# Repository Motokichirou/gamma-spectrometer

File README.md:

<h1 align="center">Гамма-спектрометр на NaI(Tl)</h1>

<p align="center">

</p>

<!-- README-I18N:START -->
<p align="center"><b>Русский</b> | <a href="./README.en.md">English</a></p>
<!-- README-I18N:END -->

Портативный цилиндрический гамма-спектрометр на кристалле NaI(Tl) Ø63×63 мм и ФЭУ Hamamatsu R1307, с интерфейсом USB-C, совместимым с [BecqMoni](https://github.com/Am6er/BecqMoni) / AtomSpectra (протокол shproto).

> 📚 **Документация:** [обзор аппаратной части](docs/ru/hardware.md) · [прошивка](docs/ru/firmware.md) · [протокол shproto](docs/ru/protocol.md) · [ПО на PC](host/README.md)

> ✅ **Ноябрь 2026: прибор собран и работает с BecqMoni** на штатном детекторе NaI(Tl) Ø63×63 + R1307 (ФЭУ ~565 В):
> **Cs-137 6.7–6.9 % FWHM**. Разбор хвостовых наложений в прошивке: на смеси ~20 кимп/с принимается ~17 400 имп/с
> без потери разрешения; поправка нелинейности кодов АЦП (DNL). Подробности — журнал [`SPEC.md`](firmware/board_g474cb/SPEC.md) §10.

---

## Ключевые характеристики

| Параметр | Значение |
|---|---|
| Детектор | NaI(Tl) Ø63×63 мм |
| ФЭУ | Hamamatsu R1307 (8 каскадов, Ø76 мм) |
| Диапазон энергий | ≈20 кэВ (порог 18 кодов) – ≈3.8 МэВ (насыщение АЦП) |
| FWHM @ Cs-137 | **6.7–6.9 % измерено** (штатный NaI 63×63 + R1307, ВВ ~565 В) |
| Каналов спектра | 8192 |
| Скорость счёта | до ~30 000 имп/с |
| МК | STM32G474CBT6 (LQFP-48) @ 156 МГц, 12-бит АЦП (сигнал 3.47 Мвыб/с), встроенные ОУ |
| ВВ питание | 0 … −1200 В, рабочее ~565 В на штатном ФЭУ (MAX1847 + 4-ступенчатый умножитель CW) |
| Интерфейс | USB-C → UART 600 кбит/с (FT231X), протокол shproto |
| Питание | USB 5 В, ~370 мА |
| Форм-фактор | Цилиндрический стек, платы Ø45 мм |

---

## Аппаратная архитектура

### Стек плат (снизу → вверх)

```
 ┌─────────────────────────────────────────┐
 │  USB/Power board  Ø45 mm               │  ← кабель USB-C
 │  LP5907 · AMS1117 · TPS60400 · FT231X  │
 ├─────────────────────────────────────────┤
 │  HV board         Ø45 mm               │
 │  MAX1847 · IRLML0060 · CW ×4 · ≤−1200 V│
 ├─────────────────────────────────────────┤
 │  MCU board        Ø45 mm               │
 │  STM32G474CBT6 · шейпер · ADC · SPI    │
 ├─────────────────────────────────────────┤
 │  Divider board    Ø42–45 mm            │  ← ФЭУ Hamamatsu R1307 + NaI(Tl)
 │  R1307 divider · MMBTA42 buffers       │
 │  ADA4817-1 TIA (Zt = 2.7 kΩ)           │
 └─────────────────────────────────────────┘
```

Межплатные соединения — без разъёмов:
- **Шина стека**: цанговые пины Ø1.5 мм на дуге R20 мм, соосные на всех платах (44 посадочных
  места: USB 11, ВВ 15, МК 13, делитель 5); по ней же идёт питание делителя ±5 В_A
- **Сигнал** (делитель → МК): тонкий коаксиал, припаянный к пятакам
- **−HV**: экранированный провод ≥5 кВ (ВВ → делитель) через отверстие Ø4.5 мм в плате МК
- **Pt1000** на корпусе кристалла: витая пара на пятаки платы МК
- Механика: по три стойки M2.5 в центре каждой платы

### Цепь сигнала

```
NaI(Tl) + R1307            Плата делителя                 Плата МК
─────────────    ─────────────────────────────   ──────────────────────────────────
 Сцинтилляция →   Делитель (цепочка 7.72 МОм)   →  OPAMP1: интегратор, τ=1 мкс
 τ_спада=230 нс   Активные буферы (Dy6/7/8)        OPAMP2: интегратор, τ=1.8 мкс
 ФЭУ на ~565 В    ADA4817 TIA, Zt=2.7 кОм       →  PGA ×4 (OPAMP3)
                                                   V_ADC = baseline 0.394 В
                                                   ADC3_IN1, 3.47 Мвыб/с
                                                   импульс: фронт 5–6 отсчётов, FWHM 3.6 мкс
                                                   амплитуда по эталону формы (64 фазы)
                                                   гистограмма 8192 кан. → USB
```

**Полярность АЦП:** анод забирает ток ⇒ выход TIA вверх ⇒ импульсы **положительны** относительно baseline 0.394 В → `amplitude = sample − baseline`

### Калибровка энергии (измерено на прежнем временном детекторе NaI 40×40, ~755 В, Ra-226)

Калибровка по 5 точкам в BecqMoni: `E[кэВ] = −6.01 + 0.5518·x + 6.63·10⁻⁶·x²` (x — канал).
Изгиб шкалы — в основном непропорциональность световыхода NaI, а не электроника.

| Линия | Энергия | Канал / 8192 | Найдено по калибровке |
|---|---|---|---|
| Pb-214 | 295 кэВ | 549 | 299 кэВ |
| Pb-214 | 352 кэВ | 652 | 356 кэВ |
| Bi-214 | 609 кэВ | 1102 | 610 кэВ |
| Cs-137 | 662 кэВ | ≈1194 | — |
| Bi-214 | 1120 кэВ | 1990 | 1118 кэВ |
| Bi-214 | 1764 кэВ | 3107 | 1773 кэВ |
| Потолок (насыщение АЦП) | ≈3.8 МэВ | ≈6900 | — |

Положение пиков задаётся ВВ: Cs выставляется на канал ~1160–1200 подстройкой ВВ (на штатном детекторе — ~565 В).

---

## Статус проекта

| Задача | Статус |
|---|---|
| Схемы всех 4 плат | ✅ Готово (ERC 0) |
| LTspice: TIA + активный делитель, шейпер, шум, петля ВВ | ✅ До разводки; итог подтверждён замерами на плате |
| BOM с MPN + footprint | ✅ 176 компонентов. Себестоимость прибора **6 749 ₽** деньгами (8 540 ₽ с учётом домашних запасов, без детектора) — [`docs/cost.md`](docs/cost.md) |
| Разводка PCB | ✅ 2 слоя, 4 платы в одной заготовке 187.5 × 45 мм, нормы ВВ-зазоров 3 мм/кВ в `.kicad_dru`. Плата МК переразведена под LQFP-48 (октябрь 2026) |
| Изготовление плат | ✅ Получены (ПС-Электро, 1.5 мм, без шелкографии) |
| Комплектующие | ✅ Всё получено и сверено |
| Сборка и первое включение | ✅ Стек собран, прошивка по UART через системный загрузчик, ВВ под нагрузкой, тракт исправен |
| Прошивка STM32 | ✅ Чистая прошивка [`firmware/gamma_fw/`](firmware/gamma_fw/) на плате: детектор с эталоном формы (снят с реального тракта), разбор хвостовых наложений, поправка DNL АЦП, ВВ с подстройкой, Pt1000, регистратор спектров во флешку W25Q64, настройки (v4) и калибровка во флеш, обновление по COM-порту; принимается BecqMoni. ТЗ и журнал находок — [`firmware/board_g474cb/SPEC.md`](firmware/board_g474cb/SPEC.md) |
| Доводка тракта | ✅ Шейпер переделан под длинное формирование, R417 2.7 кОм: Cs 7.8 → 6.9 % (на 40×40), ВВ 1030 → ~750 В |
| Штатный детектор NaI 63×63 + R1307 | ✅ Установлен с 2026-11-09, ВВ ~565 В, Cs-137 6.7–6.9 % FWHM. Остаётся термокомпенсация и доводка ревизии плат — [`docs/revision_todo.md`](docs/revision_todo.md) |
| ПО на PC `gammapult` | ✅ Релиз v0.7.0: сервисный пульт под боевую прошивку (GUI + CLI, единый .exe; новый интерфейс — главный экран, мастер настройки, расширенный режим): телеметрия, ВВ и подстройка по пику, калибровки монитора ВВ и Pt1000, порог/PGA, самотест линейности по ЦАП, мастера эталона формы и термокомпенсации, **прошивка голого прибора и мастер ввода в строй**, сохранение во флеш. Спектры и энергокалибровка — в BecqMoni |

---

## Структура репозитория

```
gamma-spectrometer/
├── docs/
│   ├── adc_mcu_board.md              # Плата МК v1.6 — полная техническая документация
│   ├── divider_board.md              # Плата делителя + ADA4817 TIA
│   ├── usb_power_board.md            # Плата USB/питания — обзор
│   ├── usb_power_board_schematic.md  # Плата USB/питания — детальная схема
│   ├── hv_board_schematic.md         # Плата ВВ — детальная схема
│   ├── mcu_board_bringup.md          # Запуск платы МК (первое включение, доработки)
│   ├── hv_board_bringup.md           # Запуск платы ВВ, помеха 257 кГц и экран
│   ├── assembly_notes.md             # Заметки по сборке
│   ├── fab_pselectro.md              # Требования завода и сверка
│   ├── cost.md                       # Себестоимость
│   └── ru/, en/                      # Курированная документация (RU/EN)
├── firmware/
│   ├── board_g474cb/SPEC.md          # ТЗ прошивки и журнал находок
│   └── gamma_fw/                     # Боевая прошивка (сборка build.sh, тесты на ПК, tools/gfw.py)
├── host/                             # ПО на PC `gammapult` (Win32/ImGui, GUI + CLI)
├── pcb/
│   └── gamma_spectrometer/           # Проект KiCad (все 4 платы, заготовка, герберы)
```

---

## Разрешение (измерено, Cs-137)

Строки до «Тот же детектор Sypher» включительно — на временном кристалле NaI 40×40.

| Конфигурация | FWHM |
|---|---|
| Первый тракт (импульс короче отсчёта АЦП), ~1040 В | 7.6–7.8 % |
| Шейпер V2 (фронт 5–6 отсчётов), 1030 В | 6.99 % |
| Шейпер V2 + R417 2.7 кОм, ~755 В | 7.1 % |
| То же, кристалл 40×40 с большим световыходом, 735 В | **6.9 %** |
| Тот же детектор Sypher на своей электронике (по энергии, кэВ) | 7.08 % |
| **Штатный NaI 63×63 + R1307**, ~565 В (с 2026-11-09) | **6.7–6.9 %** |

На штатном детекторе шум базы σ ≈ 2.2 кода АЦП при амплитуде Cs ≈ 595 кодов: вклад электроники
не больше ≈0.9 % FWHM (оценка сверху, подгонка по эталону ещё усредняет), а из 6.7–6.9 % на кристалл
и ФЭУ приходится ≈6.7 %. Разрешение ограничено детектором, а не трактом (на 40×40 скан ВВ давал то же:
a ≈ 7.0 %, шум ≈0.8 %). Разрешение сравнивается только по энергии: у трактов с нелинейной шкалой процент
по каналу выглядит лучше реального. Подробности — [`firmware/board_g474cb/SPEC.md`](firmware/board_g474cb/SPEC.md) §10.

---

## Протокол: shproto / AtomSpectra

Совместим с [BecqMoni](https://github.com/Am6er/BecqMoni) и [nanopro](https://github.com/Am6er/nanopro).

- UART 600 000 бит/с, 8N1
- Кадр: `0xFE | CMD | PAYLOAD (с байт-стаффингом) | CRC16-MODBUS | 0xA5`
- Cmd `0x01`: спектр (до 8192 × 32-битных каналов)
- Cmd `0x04`: статус (прошедшее время, CPS, число невалидных импульсов)
- Keep-alive: `0xFF` от ПК каждую ~1 с
- Необязательная команда `-baud` (до 3 Мбод) действует только в ОЗУ: через 5 с без кадров от хоста прибор возвращается на 600 000

Полный справочник: [docs/ru/protocol.md](docs/ru/protocol.md).

---

## Лицензия

Файлы аппаратного дизайна (KiCad, LTspice) — [CERN OHL-S v2](https://ohwr.org/cern_ohl_s_v2.txt)  
ПО (прошивка, host) — [MIT](https://opensource.org/licenses/MIT)

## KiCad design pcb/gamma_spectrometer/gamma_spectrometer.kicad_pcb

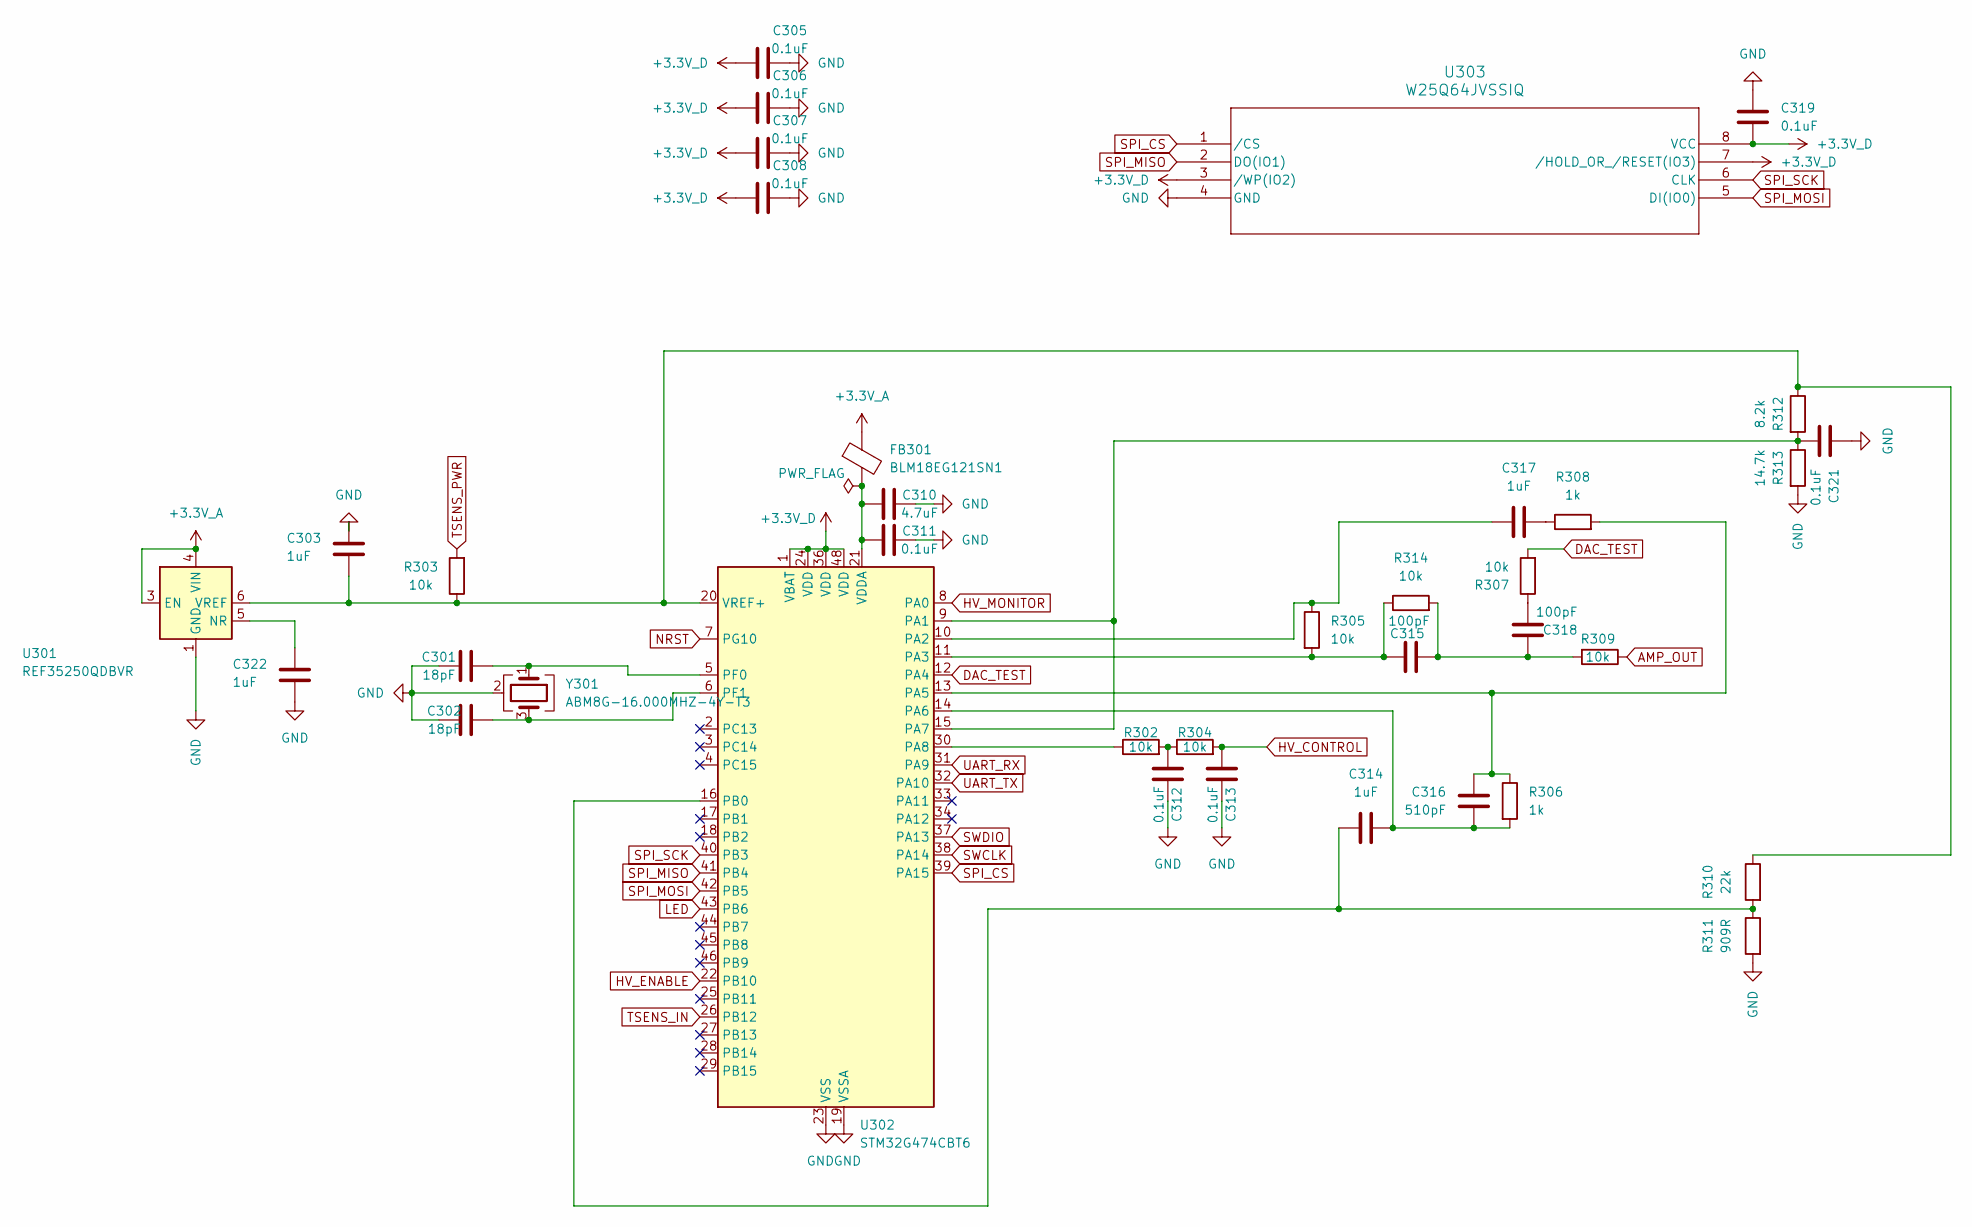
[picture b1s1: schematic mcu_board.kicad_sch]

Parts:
C301, C302: 18pF; C_0402_1005Metric_Pad0.74x0.62mm_HandSolder
C303, C322: 1uF; C_0805_2012Metric_Pad1.18x1.45mm_HandSolder
C305, C306, C307, C308, C311, C312, C313, C319, C321: 0.1uF; C_0603_1608Metric_Pad1.08x0.95mm_HandSolder
C310: 4.7uF; C_0805_2012Metric_Pad1.18x1.45mm_HandSolder
C314, C317: 1uF; C_0603_1608Metric_Pad1.08x0.95mm_HandSolder
C315, C318: 100pF; C_0603_1608Metric_Pad1.08x0.95mm_HandSolder
C316: 510pF; C_0603_1608Metric_Pad1.08x0.95mm_HandSolder
FB301: BLM18EG121SN1; L_0603_1608Metric_Pad1.05x0.95mm_HandSolder
R302, R303, R304, R305, R307, R309, R314: 10k; R_0603_1608Metric_Pad0.98x0.95mm_HandSolder
R306, R308: 1k; R_0603_1608Metric_Pad0.98x0.95mm_HandSolder
R310: 22k; R_0603_1608Metric_Pad0.98x0.95mm_HandSolder
R311: 909R; R_0603_1608Metric_Pad0.98x0.95mm_HandSolder
R312: 8.2k; R_0603_1608Metric_Pad0.98x0.95mm_HandSolder
R313: 14.7k; R_0603_1608Metric_Pad0.98x0.95mm_HandSolder
U301: REF35250QDBVR; SOT-23-6
U302: STM32G474CBT6; LQFP-48_7x7mm_P0.5mm
U303: W25Q64JVSSIQ; SOIC-8_5P28X5P28_WIN-M
Y301: ABM8G-16.000MHZ-4Y-T3; Crystal_SMD_3225-4Pin_3.2x2.5mm

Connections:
+3.3V_A: FB301.1, U301.3 (EN), U301.4 (VIN); also elsewhere on the board
+3.3V_D: C305.1, C306.1, C307.1, C308.1, C319.2, U302.1 (VBAT), U302.24 (VDD), U302.36 (VDD), U302.48 (VDD), U303.3 (/WP(IO2)), U303.7 (/HOLD_OR_/RESET(IO3)), U303.8 (VCC); also elsewhere on the board
AMP_OUT: R309.1; also elsewhere on the board
DAC_TEST: R307.2, U302.12 (PA4)
GND: C301.2, C302.2, C303.1, C305.2, C306.2, C307.2, C308.2, C310.2, C311.2, C312.2, C313.2, C319.1, C321.1, C322.2, R311.2, R313.2, U301.1 (GND), U301.2 (GND), U302.19 (VSSA), U302.23 (VSS), U302.35 (VSS), U302.47 (VSS), U303.4 (GND), Y301.2 (G), Y301.4 (G); also elsewhere on the board
HV_CONTROL: C313.1, R304.2; also elsewhere on the board
HV_ENABLE: U302.22 (PB10); also elsewhere on the board
HV_MONITOR: U302.8 (PA0); also elsewhere on the board
LED: U302.43 (PB6); also elsewhere on the board
NRST: U302.7 (PG10)
unnamed: C312.1, R302.2, R304.1
unnamed: C315.1, C318.1, R309.2, R314.2
unnamed: C317.2, R308.1
unnamed: C318.2, R307.1
unnamed: C322.1, U301.5 (NR)
unnamed: C303.2, R303.1, R310.1, R312.1, U301.6 (VREF), U302.20 (VREF+)
unnamed: C321.2, R312.2, R313.1, U302.9 (PA1), U302.15 (PA7)
unnamed: C317.1, R305.1, U302.10 (PA2)
unnamed: C315.2, R305.2, R314.1, U302.11 (PA3)
unnamed: C316.1, R306.1, R308.2, U302.13 (PA5)
unnamed: C314.2, C316.2, R306.2, U302.14 (PA6)
unnamed: R302.1, U302.30 (PA8)
unnamed: C314.1, R310.2, R311.1, U302.16 (PB0)
unnamed: C301.1, U302.5 (PF0), Y301.1
unnamed: C302.1, U302.6 (PF1), Y301.3
unnamed: C310.1, C311.1, FB301.2, U302.21 (VDDA)
SPI_CS: U302.39 (PA15), U303.1 (/CS)
SPI_MISO: U302.41 (PB4), U303.2 (DO(IO1))
SPI_MOSI: U302.42 (PB5), U303.5 (DI(IO0))
SPI_SCK: U302.40 (PB3), U303.6 (CLK)
SWCLK: U302.38 (PA14)
SWDIO: U302.37 (PA13)
TSENS_IN: U302.26 (PB12); also elsewhere on the board
TSENS_PWR: R303.2; also elsewhere on the board
UART_RX: U302.31 (PA9); also elsewhere on the board
UART_TX: U302.32 (PA10); also elsewhere on the board

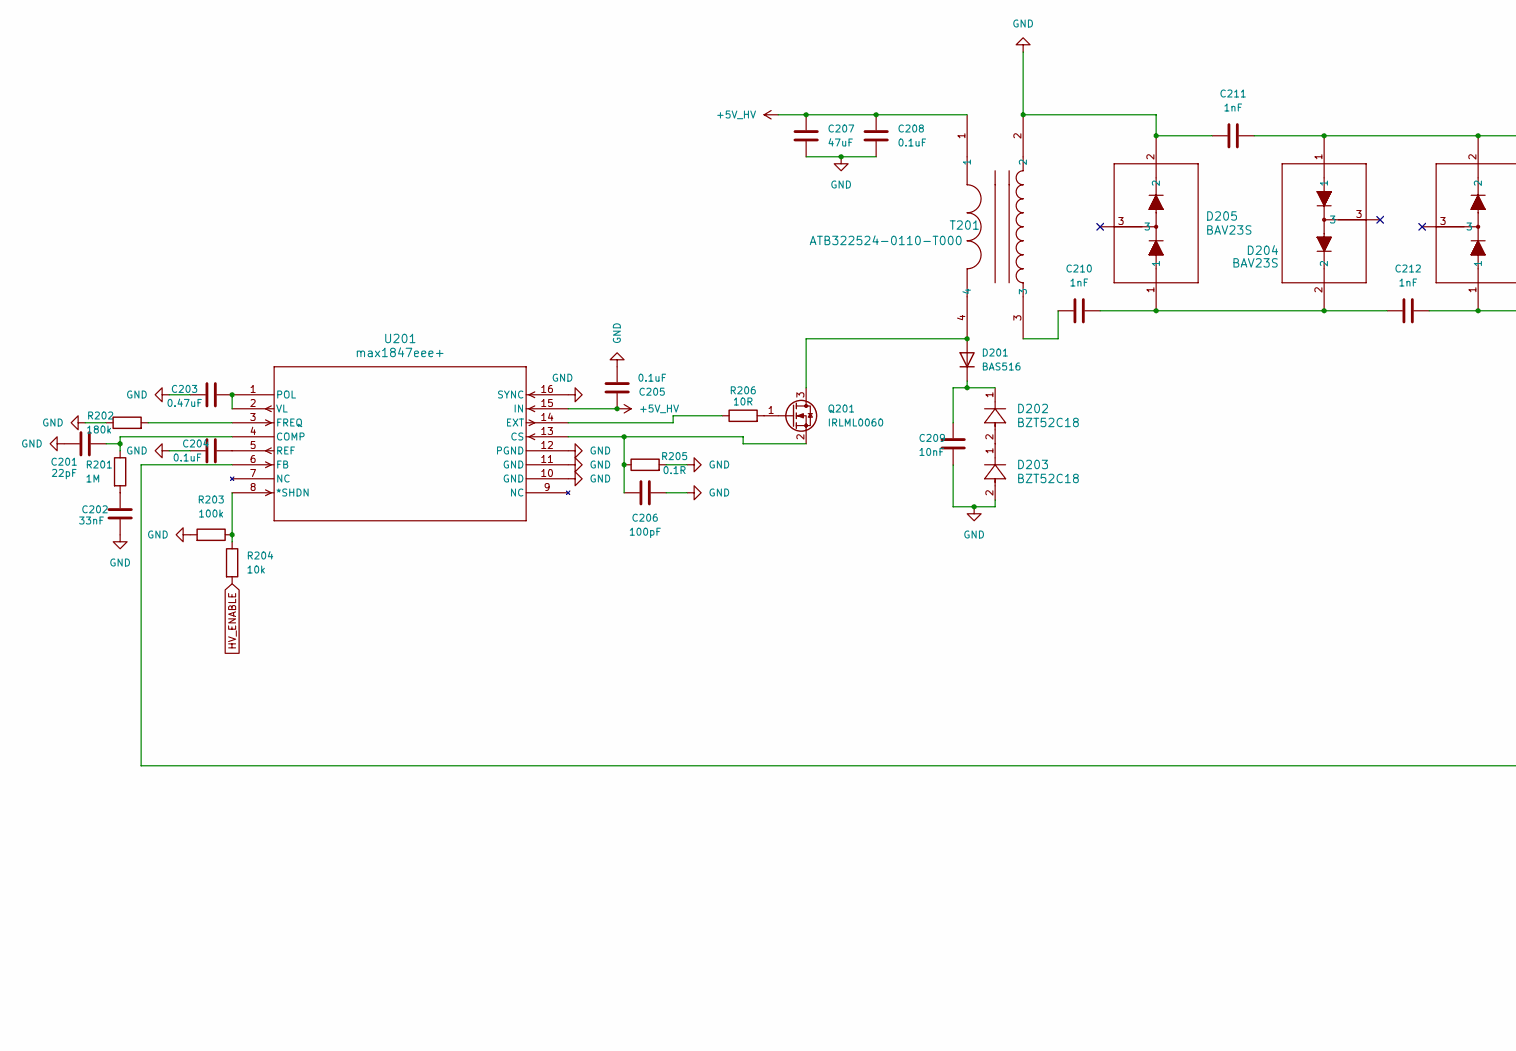
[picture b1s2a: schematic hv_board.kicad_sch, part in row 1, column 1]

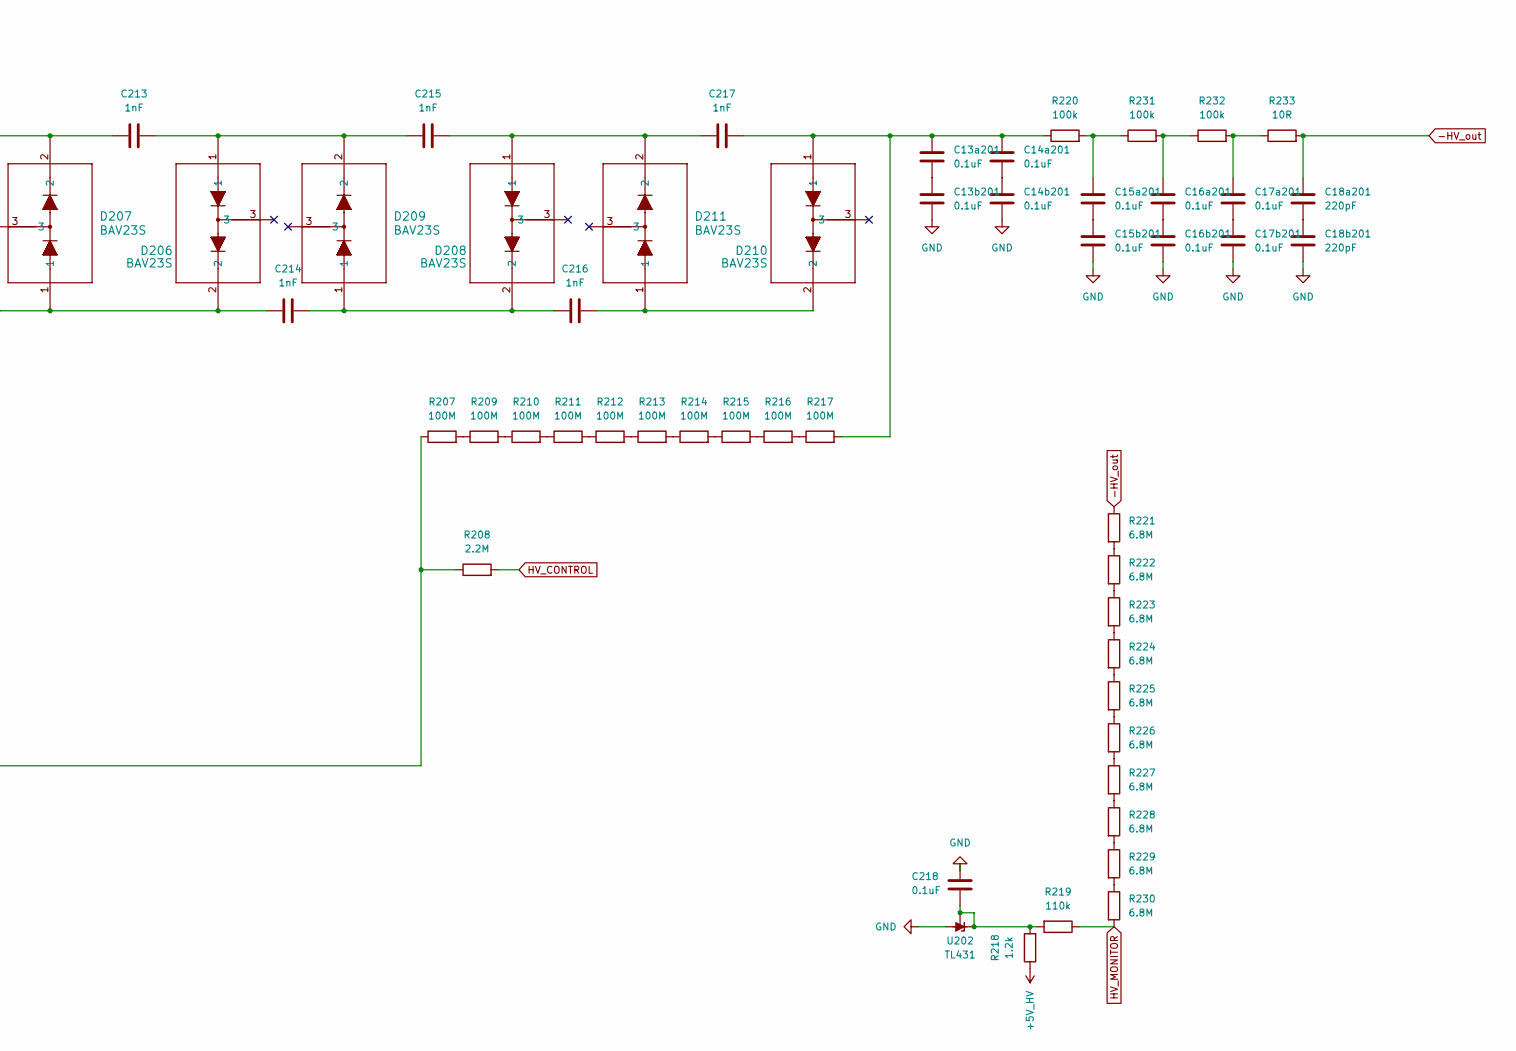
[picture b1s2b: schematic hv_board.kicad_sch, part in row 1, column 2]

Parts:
C13a201, C13b201, C14a201, C14b201, C15a201, C15b201, C16a201, C16b201, C17a201, C17b201: 0.1uF; C_1812_4532Metric_Pad1.57x3.40mm_HandSolder
C18a201, C18b201: 220pF; C_1206_3216Metric_Pad1.33x1.80mm_HandSolder
C201: 22pF; C_0402_1005Metric_Pad0.74x0.62mm_HandSolder
C202: 33nF; C_0805_2012Metric_Pad1.18x1.45mm_HandSolder
C203: 0.47uF; C_0805_2012Metric_Pad1.18x1.45mm_HandSolder
C204, C205, C208, C218: 0.1uF; C_0603_1608Metric_Pad1.08x0.95mm_HandSolder
C206: 100pF; C_0603_1608Metric_Pad1.08x0.95mm_HandSolder
C207: 47uF; C_1210_3225Metric_Pad1.33x2.70mm_HandSolder
C209: 10nF; C_0603_1608Metric_Pad1.08x0.95mm_HandSolder
C210, C211, C212, C213, C214, C215, C216, C217: 1nF; C_0805_2012Metric_Pad1.18x1.45mm_HandSolder
D201: BAS516; D_SOD-523
D202, D203: BZT52C18; D_SOD-123
D204, D205, D206, D207, D208, D209, D210, D211: BAV23S; SOT-23
Q201: IRLML0060; SOT-23
R201: 1M; R_0603_1608Metric_Pad0.98x0.95mm_HandSolder
R202: 180k; R_0603_1608Metric_Pad0.98x0.95mm_HandSolder
R203, R220, R231, R232: 100k; R_0603_1608Metric_Pad0.98x0.95mm_HandSolder
R204: 10k; R_0603_1608Metric_Pad0.98x0.95mm_HandSolder
R205: 0.1R; R_0603_1608Metric_Pad0.98x0.95mm_HandSolder
R206, R233: 10R; R_0603_1608Metric_Pad0.98x0.95mm_HandSolder
R207, R209, R210, R211, R212, R213, R214, R215, R216, R217: 100M; R_1206_3216Metric_Pad1.30x1.75mm_HandSolder
R208: 2.2M; R_0603_1608Metric_Pad0.98x0.95mm_HandSolder
R218: 1.2k; R_0603_1608Metric_Pad0.98x0.95mm_HandSolder
R219: 110k; R_0603_1608Metric_Pad0.98x0.95mm_HandSolder
R221, R222, R223, R224, R225, R226, R227, R228, R229, R230: 6.8M; R_1206_3216Metric_Pad1.30x1.75mm_HandSolder
T201: ATB322524-0110-T000; CHOKE_524-0110-T000_TDK-M
U201: max1847eee+; 21-0055H_16_MXM-M
U202: TL431; SOT-23

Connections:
+5V_HV: C205.2, C207.1, C208.1, R218.1, T201.1, U201.15 (IN); also elsewhere on the board
GND: C13b201.2, C14b201.2, C15b201.2, C16b201.2, C17b201.2, C18b201.2, C201.1, C202.2, C203.1, C204.1, C205.1, C206.2, C207.2, C208.2, C209.2, C211.1, C218.1, D203.2, D205.2, R202.1, R203.2, R205.2, T201.2, U201.10 (GND), U201.11 (GND), U201.12 (PGND), U201.16 (SYNC), U202.3 (A); also elsewhere on the board
HV_CONTROL: R208.2; also elsewhere on the board
HV_ENABLE: R204.2; also elsewhere on the board
HV_MONITOR: R219.1, R230.2; also elsewhere on the board
unnamed: C13a201.1, C14a201.1, C217.2, D210.1, R217.2, R220.1
unnamed: C13a201.2, C13b201.1
unnamed: C14a201.2, C14b201.1
unnamed: C15a201.1, R220.2, R231.1
unnamed: C15a201.2, C15b201.1
unnamed: C16a201.1, R231.2, R232.1
unnamed: C16a201.2, C16b201.1
unnamed: C17a201.1, R232.2, R233.1
unnamed: C17a201.2, C17b201.1
unnamed: C18a201.2, C18b201.1
unnamed: C202.1, R201.2
unnamed: C210.1, T201.3
unnamed: C210.2, C212.1, D204.2, D205.1
unnamed: C211.2, C213.1, D204.1, D207.2
unnamed: C212.2, C214.1, D206.2, D207.1
unnamed: C213.2, C215.1, D206.1, D209.2
unnamed: C214.2, C216.1, D208.2, D209.1
unnamed: C215.2, C217.1, D208.1, D211.2
unnamed: C216.2, D210.2, D211.1
unnamed: D201.2 (A), Q201.3 (D), T201.4
unnamed: C209.1, D201.1 (K), D202.1
unnamed: D202.2, D203.1
unnamed: Q201.1 (G), R206.2
unnamed: C206.1, Q201.2 (S), R205.1, U201.13 (CS)
unnamed: R207.2, R209.1
unnamed: R209.2, R210.1
unnamed: R210.2, R211.1
unnamed: R211.2, R212.1
unnamed: R212.2, R213.1
unnamed: R213.2, R214.1
unnamed: R214.2, R215.1
unnamed: R215.2, R216.1
unnamed: R216.2, R217.1
unnamed: R221.2, R222.1
unnamed: R222.2, R223.1
unnamed: R223.2, R224.1
unnamed: R224.2, R225.1
unnamed: R225.2, R226.1
unnamed: R226.2, R227.1
unnamed: R227.2, R228.1
unnamed: R228.2, R229.1
unnamed: R229.2, R230.1
unnamed: R203.1, R204.1, U201.8 (*SHDN)
unnamed: C201.2, R201.1, U201.4 (COMP)
unnamed: R206.1, U201.14 (EXT)
unnamed: R207.1, R208.1, U201.6 (FB)
unnamed: R202.2, U201.3 (FREQ)
unnamed: C203.2, U201.1 (POL), U201.2 (VL)
unnamed: C204.2, U201.5 (REF)
unnamed: C218.2, R218.2, R219.2, U202.1 (K), U202.2 (REF)
−HV_out: C18a201.1, R221.1, R233.2; also elsewhere on the board

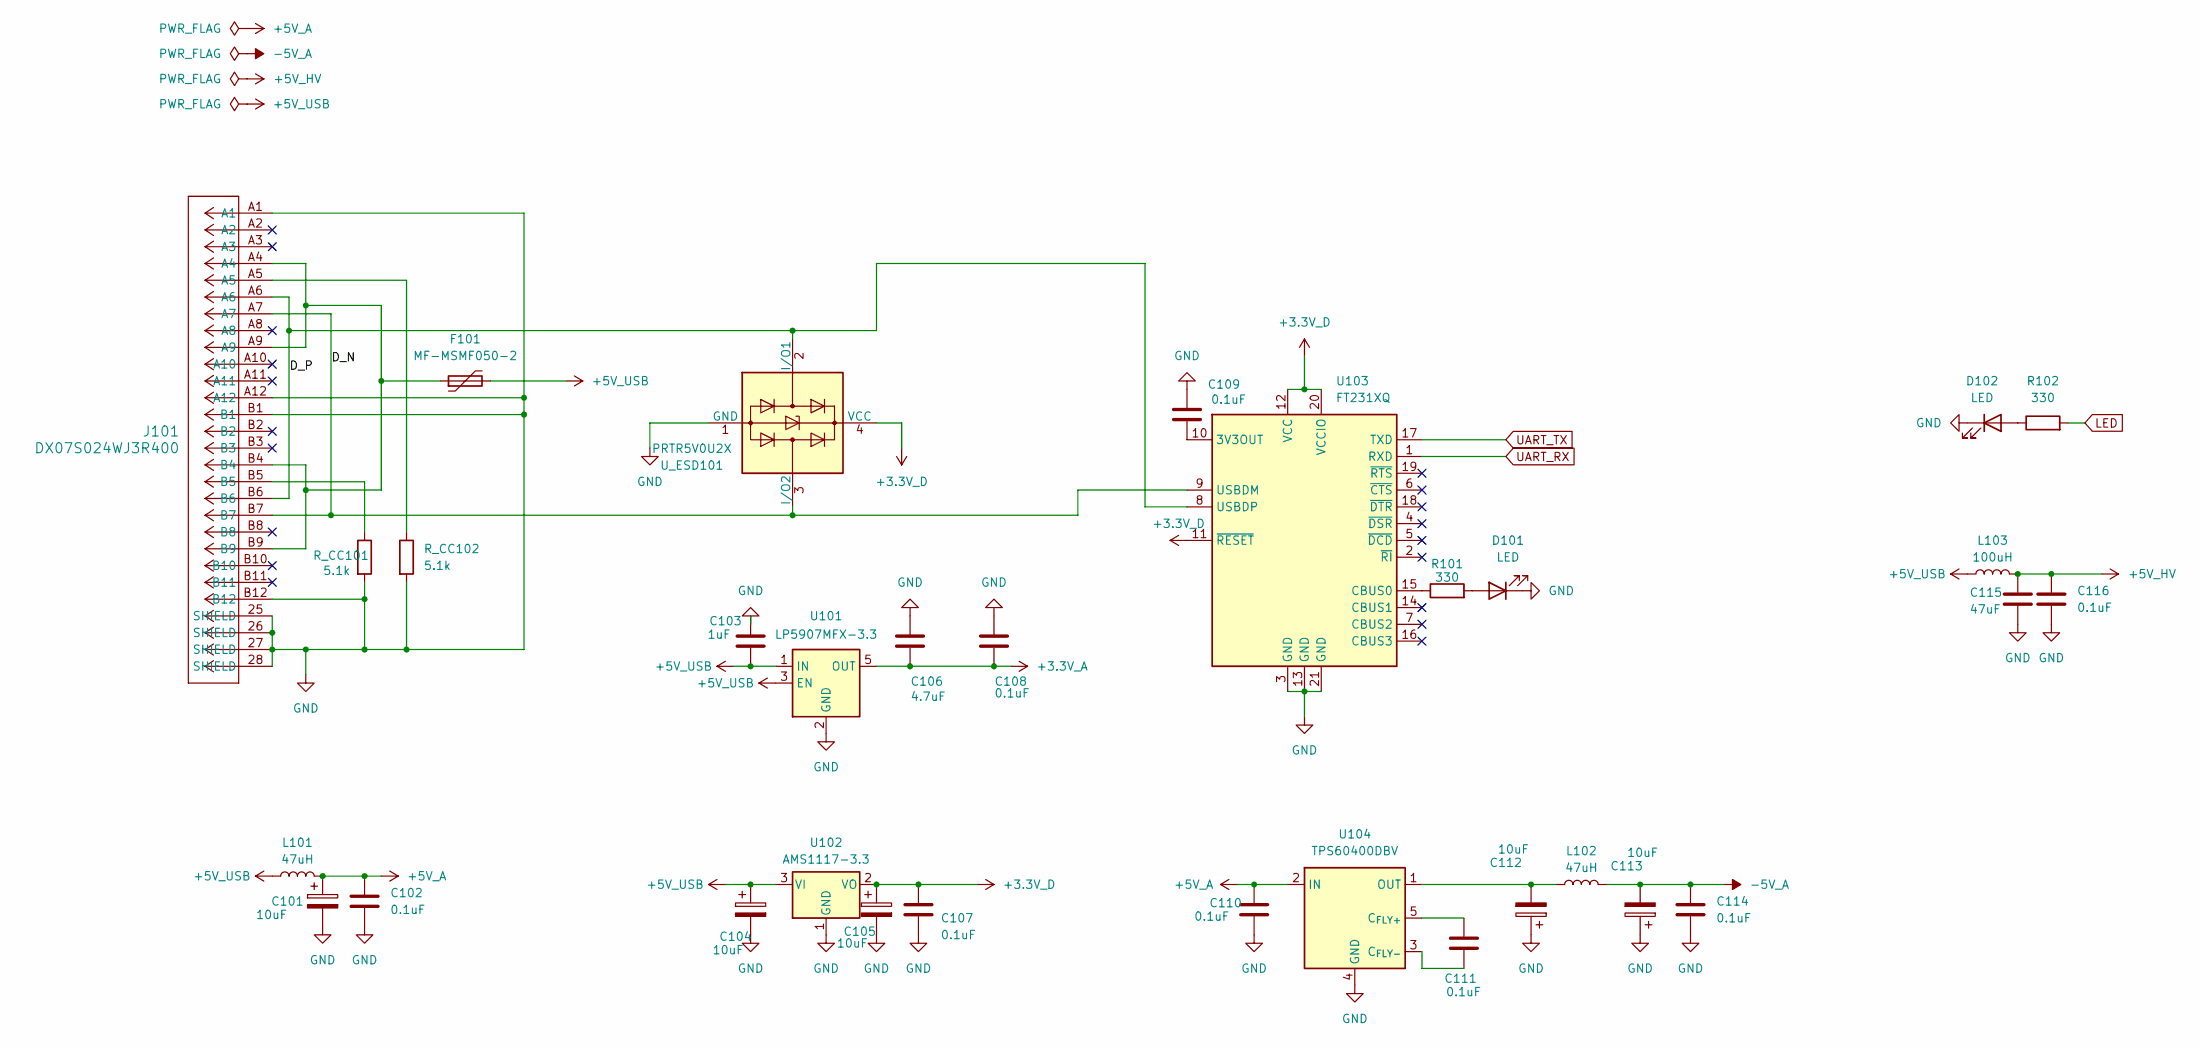
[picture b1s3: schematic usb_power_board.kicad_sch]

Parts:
C101, C104, C105, C112, C113: 10uF; CP_EIA-3528-21_Kemet-B_HandSolder
C102, C107, C108, C109, C110, C111, C114, C116: 0.1uF; C_0603_1608Metric_Pad1.08x0.95mm_HandSolder
C103: 1uF; C_0805_2012Metric_Pad1.18x1.45mm_HandSolder
C106: 4.7uF; C_0805_2012Metric_Pad1.18x1.45mm_HandSolder
C115: 47uF; C_1210_3225Metric_Pad1.33x2.70mm_HandSolder
D101, D102: LED; LED_0805_2012Metric_Pad1.15x1.40mm_HandSolder
F101: MF-MSMF050-2; Fuse_1812_4532Metric_Pad1.30x3.40mm_HandSolder
J101: DX07S024WJ3R400; USB_C_Receptacle_JAE_DX07S024WJ3R400
L101, L102: 47uH; L_Neosid_SMS-ME3015
L103: 100uH; L_Bourns_SRU5016_5.2x5.2mm
R101, R102: 330; R_0603_1608Metric_Pad0.98x0.95mm_HandSolder
R_CC101, R_CC102: 5.1k; R_0603_1608Metric_Pad0.98x0.95mm_HandSolder
U101: LP5907MFX-3.3; SOT-23-5
U102: AMS1117-3.3; SOT-223-3_TabPin2
U103: FT231XQ; QFN-20-1EP_4x4mm_P0.5mm_EP2.5x2.5mm
U104: TPS60400DBV; SOT-23-5
U_ESD101: PRTR5V0U2X; SOT-143

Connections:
+3.3V_A: C106.2, C108.2, U101.5 (OUT); also elsewhere on the board
+3.3V_D: C105.1, C107.1, U102.2 (VO), U103.11 (~RESET), U103.12 (VCC), U103.20 (VCCIO), U_ESD101.4 (VCC); also elsewhere on the board
+5V_A: C101.1, C102.1, C110.1, L101.2, U104.2 (IN); also elsewhere on the board
+5V_HV: C115.1, C116.1, L103.2; also elsewhere on the board
+5V_USB: C103.2, C104.1, F101.2, L101.1, L103.1, U101.1 (IN), U101.3 (EN), U102.3 (VI)
/USB_Power_Board/D_N: J101.A7, J101.B7, U103.9 (USBDM), U_ESD101.3 (I/O2)
/USB_Power_Board/D_P: J101.A6, J101.B6, U103.8 (USBDP), U_ESD101.2 (I/O1)
GND: C101.2, C102.2, C103.1, C104.2, C105.2, C106.1, C107.2, C108.1, C109.2, C110.2, C112.1, C113.1, C114.2, C115.2, C116.2, D101.1 (K), D102.1 (K), J101.25 (SHIELD), J101.26 (SHIELD), J101.27 (SHIELD), J101.28 (SHIELD), J101.A1, J101.A12, J101.B1, J101.B12, R_CC101.2, R_CC102.2, U101.2 (GND), U102.1 (GND), U103.3 (GND), U103.13 (GND), U103.21 (GND), U104.4 (GND), U_ESD101.1 (GND); also elsewhere on the board
LED: R102.2; also elsewhere on the board
unnamed: D101.2 (A), R101.2
unnamed: D102.2 (A), R102.1
unnamed: F101.1, J101.A4, J101.A9, J101.B4, J101.B9
unnamed: J101.A5, R_CC102.1
unnamed: J101.B5, R_CC101.1
unnamed: C109.1, U103.10 (3V3OUT)
unnamed: R101.1, U103.15 (CBUS0)
unnamed: C111.1, U104.5 (C_{FLY+})
unnamed: C111.2, U104.3 (C_{FLY-})
unnamed: C112.2, L102.1, U104.1 (OUT)
UART_RX: U103.1 (RXD); also elsewhere on the board
UART_TX: U103.17 (TXD); also elsewhere on the board
−5V_A: C113.2, C114.1, L102.2; also elsewhere on the board

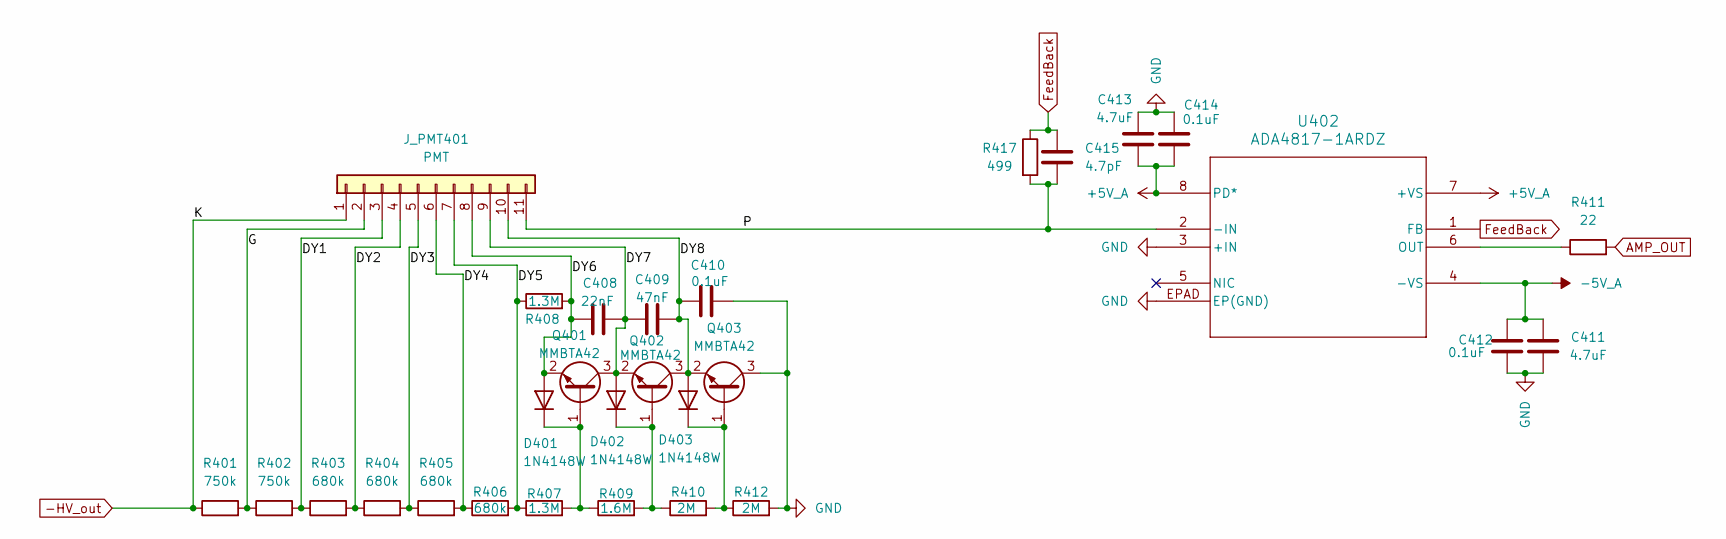
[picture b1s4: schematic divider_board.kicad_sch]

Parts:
C408: 22nF; C_1210_3225Metric_Pad1.33x2.70mm_HandSolder
C409: 47nF; C_1812_4532Metric_Pad1.57x3.40mm_HandSolder
C410: 0.1uF; C_1812_4532Metric_Pad1.57x3.40mm_HandSolder
C411, C413: 4.7uF; C_0805_2012Metric_Pad1.18x1.45mm_HandSolder
C412, C414: 0.1uF; C_0603_1608Metric_Pad1.08x0.95mm_HandSolder
C415: 4.7pF; C_0402_1005Metric_Pad0.74x0.62mm_HandSolder
D401, D402, D403: 1N4148W; D_SOD-123
J_PMT401: PMT; J_PMT401_R1307-01
Q401, Q402, Q403: MMBTA42; SOT-23
R401, R402: 750k; R_1206_3216Metric_Pad1.30x1.75mm_HandSolder
R403, R404, R405, R406: 680k; R_1206_3216Metric_Pad1.30x1.75mm_HandSolder
R407, R408: 1.3M; R_1206_3216Metric_Pad1.30x1.75mm_HandSolder
R409: 1.6M; R_1206_3216Metric_Pad1.30x1.75mm_HandSolder
R410, R412: 2M; R_1206_3216Metric_Pad1.30x1.75mm_HandSolder
R411: 22; R_0402_1005Metric_Pad0.72x0.64mm_HandSolder
R417: 499; R_0603_1608Metric_Pad0.98x0.95mm_HandSolder
U402: ADA4817-1ARDZ; RD_8_1_ADI-M

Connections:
+5V_A: C413.1, C414.1, U402.7 (+VS), U402.8 (PD*); also elsewhere on the board
/Divider_Board/DY1: J_PMT401.3, R402.2, R403.1
/Divider_Board/DY2: J_PMT401.4, R403.2, R404.1
/Divider_Board/DY3: J_PMT401.5, R404.2, R405.1
/Divider_Board/DY4: J_PMT401.6, R405.2, R406.1
/Divider_Board/DY5: J_PMT401.7, R406.2, R407.1, R408.1
/Divider_Board/DY6: C408.1, D401.2 (A), J_PMT401.8, Q401.2 (E), R408.2
/Divider_Board/DY7: C408.2, C409.1, D402.2 (A), J_PMT401.9, Q401.3 (C), Q402.2 (E)
/Divider_Board/DY8: C409.2, C410.1, D403.2 (A), J_PMT401.10, Q402.3 (C), Q403.2 (E)
/Divider_Board/G: J_PMT401.2, R401.2, R402.1
/Divider_Board/P: C415.1, J_PMT401.11, R417.2, U402.2 (-IN)
AMP_OUT: R411.2; also elsewhere on the board
FeedBack: C415.2, R417.1, U402.1 (FB)
GND: C410.2, C411.1, C412.1, C413.2, C414.2, Q403.3 (C), R412.2, U402.3 (+IN), U402.EPAD (EP(GND)); also elsewhere on the board
unnamed: D401.1 (K), Q401.1 (B), R407.2, R409.1
unnamed: D402.1 (K), Q402.1 (B), R409.2, R410.1
unnamed: D403.1 (K), Q403.1 (B), R410.2, R412.1
unnamed: R411.1, U402.6 (OUT)
−5V_A: C411.2, C412.2, U402.4 (-VS); also elsewhere on the board
−HV_out: J_PMT401.1, R401.1; also elsewhere on the board
